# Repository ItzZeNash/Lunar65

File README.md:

# Lunar65
A keyboard made for personal use and sounds good, as I dont have a keyboard. 65% for optimal usability.
Render/Image

Images of Schem And PCB

# Build Guide

| No | Name | Spec | Quantity |
| ----- | ----- | ----- | ----- |
| 1 | Aluminum case | Aluminum | 1 |
| 2 | Main PCB | Hotswap socket compatible, 1.6 mm thick | 1 |
| 3 | Plate | Polycarbonate, 1.5mm thick | 1 |
| 4 | PCB foam | Poron, 3mm thick | 1 |
| 5 | Switch foam | Polyethylene or Poron, 0.5mm thick | 1 |
| 6 | Case foam | Poron, 1.5mm thick | 1 |
| 7 | Socket foam | Poron, 1.5mm thick | 1 |
| 8 | O-ring | AS568-264-VMQ-A30 | 1 |
| 9 | USB-C daughter board | [Unified Daughterboard C3](https://github.com/ai03-2725/Unified-Daughterboard) | 1 |
| 10 | JST cable | JST-SH, 4pin, double-side female connector, reverse direction, 10cm | 1 |
| 11 | Screws | m2 4mm, for USB-C daughter board | 4 |
| 12 | Rubber feet(Bumpons) | 3M SJ5302, diameter 8mm, height 2mm | 4 |

### Parts
| Name | Spec | Quantity |
| ----- | ----- | ----- |
| Key switch | CherryMX compatible key switch, 5pins(recommended) | 67 |
| Keycap | CherryMX compatible keycap, 1.75U Shift key(required) | 67 |
| Stabilizer | Durock V2, etc | 6.25U * 1set and 2U * 3set |
| USB cable | The connector on the keyboard side must be USB-C | 1 |
| Grease for lubrication | Krytox 205g0(recommended) | a few grams |

## Assembly Instructions
1. **Attaching rubber feet**  
   
   First attach the rubber feet to the aluminum case so that the bottom of the aluminum case is not scratched.  
   Attach the rubber feet according to the engraved circle on the four corners of the back of the aluminum case.  

1. **Pasting socket foam**  
   
   Pasting socket foam is difficult and cannot be redone.  
   There are two methods: one is to paste the entire surface and the other is to paste only a portion of the surface.  
   
   **Practice**  
   First, practice several times without peeling off the release paper on the adhesive surface.  
   
   Place the socket foam on a flat surface with the adhesive surface facing up.  
   Straighten any bent or floating parts.  
   
   Hold the four corners with the back side (part mounting surface) of the main PCB facing down.  
   Look at the main PCB from directly above, align the notch of the mount post with the main PCB, slowly put it on the foam.  

   **When pasting the entire surface**  
   Peel off the release paper on the socket foam, and paste the main PCB and socket foam according to the procedure you practiced.  
   Once pasted, it cannot be removed cleanly, so recommend not removing it, even if it is slightly displaced.  
   (even if it can be removed, the socket foam will be stretched and the position will not match)  
   
   **When pasting only a part**  
   Peel off only a part of the release paper and paste it.  
   The area to peel off is about 10 square mm per place, and the place to peel off is about 7-8 places where the width is not narrow.  
   Cut a part of the release paper with scissors and paste the main PCB and socket foam according to the procedure you practiced.

1. **Assembling the stabilizers**  
   Please refer to [this YouTube video](https://www.youtube.com/watch?v=-vhpHjlkRgQ).  
   Apply a little thick grease to the outside of the stem and the inside of the housing.  
   Insert the stem into the housing.  
   Apply a little thick grease from the tip of the wire to the part that bends at a right angle.  
   Insert the wire into the stem and fit the wire into the housing.  

1. **Installing stabilizers**  
   
   First, insert the side without screw holes into the larger stabilizer mounting holes on the main PCB.  
   Next, screw the side with screw holes from the back side of the main PCB.  
   Make sure that the stabilizer housing is not lifted off the main PCB and that there is no rattling.  

1. **Placing switch foam**  
   
   Place the switch foam on the main PCB.  
   Slide the switch foam so that it is under the stabilizer wires.  

1. **Placing PCB foam**  
   
   Place PCB foam on the main PCB in line with the stabilizer position.  

1. **Placing plate**
   
   Place the plate on the PCB foam, aligning it with the hole in the key switches.  

1. **Lubricating key switches**  
   Although not required, it is highly recommended to lubricate the key switches to improve the typing feels and sounds.  
   Please refer to [this YouTube video](https://www.youtube.com/watch?v=44Wv4OGdmu4).  

1. **Installing key switches**  
   
   Check that the holes in the switch foam align with the key switch pin holes on the main PCB.  
   Check that the pins of the key switch are straight and insert the key switch into the main PCB from the top of the plate.  
   (Be careful not to insert at an angle, as this may break the pins or damage the sockets)  
   Make sure that there are no gaps between the plate and the key switches, and between the key switches and the main PCB, viewed from the side, and that they are evenly installed.  

1. **Installing O-ring**  
   Install O-ring between main PCB and plate.  

   Around the backspace and spacebar keys, pass the O-ring through the top surface of the stabilizer, aligning it with the notch in the plate.  
   If the O-ring cannot be secured to the top of the stabilizer, proceed as is once it is in place, as it can be adjusted when the main PCB is installed in the case.  
   Make sure there is no gap and bend between the main PCB, O-ring and plate when viewed from the side.  

1. **Connecting JST cable to USB-C daughter board**  
   
   Connect JST cable to USB-C daughter board.  
   
   Since JST cable connectors have front and back sides, refer to the photo and insert the connector with the side with no exposed terminals facing up.    

1. **Installing USB-C daughter board**  
   
   With the surface of the USB-C daughter board (the side where the components are mounted) facing up, screw it into the center back of the aluminum case with four m2 4mm screws.  
   Grab the screws with tweezers to make it easier to screw them in.  

1. **Installing case foam**  
   
   Align the posts inside the aluminum case with the notches in the case foam, and put the case foam inside the aluminum case.    
   Pull the JST cable through the cutout in the case foam.  

1. **Connecting JST cable tom main PCB**  
   
   Insert the JST cable connector into the JST connector (beige color) on the back of the main PCB.  
   
   Since JST cable connectors have front and back sides, refer to the photo and insert the connector with the side with no exposed terminals facing up.    

1. **Installing main PCB to aluminum case**  
   
   With the back side of the main PCB slightly raised, pass the blocker of the aluminum case between the blocker of the main PCB and the O-ring.    
   Lift the entire main PCB slightly and put the O-ring on the front side of the main PCB over the post on the front side of the aluminum case (not visible).  
   Gently push the main PCB down until the O-ring lightly touches the post on the aluminum case (not visible).  
   
   Make sure the O-ring is not rolled up and coming out of  the plate.  

1. **Installing keycaps**  
   
   Installing the keycaps to the key switches.  

1. **Connecting USB cable**  
   
   Connect your USB cable to the keyboard and PC and now it is completed.

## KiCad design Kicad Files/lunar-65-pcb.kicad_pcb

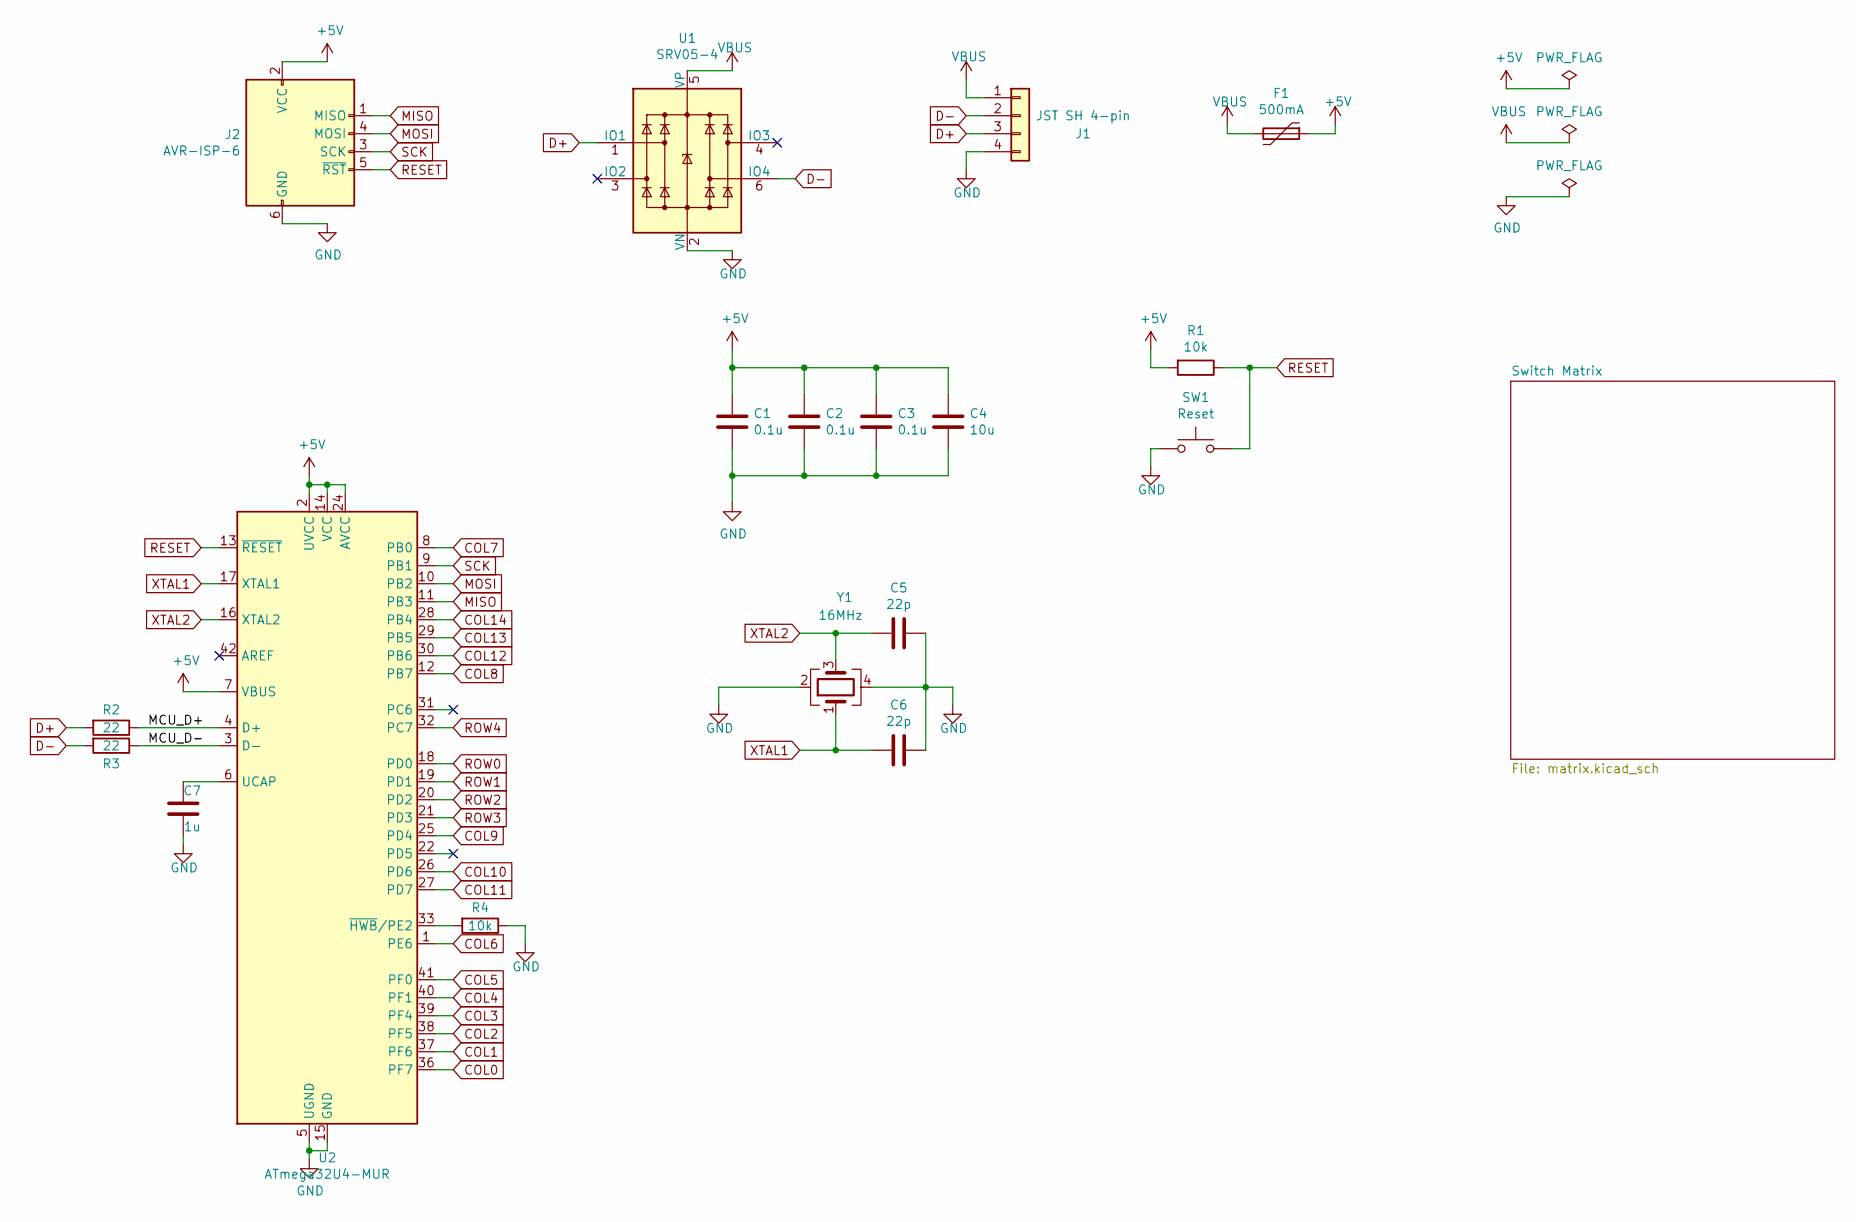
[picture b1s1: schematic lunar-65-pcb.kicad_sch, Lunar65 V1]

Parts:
C1, C2, C3: 0.1u; C_0805_2012Metric; LCSC Part # C49678
C4: 10u; C_0805_2012Metric; LCSC Part # C15850
C5, C6: 22p; C_0805_2012Metric; LCSC Part # C1804
C7: 1u; C_0805_2012Metric; LCSC Part # C28323
F1: 500mA; Fuse_1206_3216Metric; LCSC Part # C70076
J1: JST SH 4-pin; JST_SH_SM04B-SRSS-TB_1x04-1MP_P1.00mm_Horizontal; LCSC Part # C145956
J2: AVR-ISP-6; ISP
R1, R4: 10k; R_0805_2012Metric; LCSC Part # C17414
R2, R3: 22; R_0805_2012Metric; LCSC Part # C17561
SW1: Reset; SW_SPST_TL3342; LCSC Part # C318884
U1: SRV05-4; SOT-23-6; LCSC Part # C85364
U2: ATmega32U4-MUR; QFN-44-1EP_7x7mm_P0.5mm_EP5.2x5.2mm; LCSC Part # C45874
Y1: 16MHz; Crystal_SMD_3225-4Pin_3.2x2.5mm; LCSC Part # C13738

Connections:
+5V: C1.1, C2.1, C3.1, C4.1, F1.1, J2.2 (VCC), R1.2, U2.2 (UVCC), U2.7 (VBUS), U2.14 (VCC), U2.24 (AVCC), U2.34 (VCC), U2.44 (AVCC)
/MCU_D+: R2.1, U2.4 (D+)
/MCU_D-: R3.1, U2.3 (D-)
COL0: U2.36 (PF7); also elsewhere on the board
COL1: U2.37 (PF6); also elsewhere on the board
COL2: U2.38 (PF5); also elsewhere on the board
COL3: U2.39 (PF4); also elsewhere on the board
COL4: U2.40 (PF1); also elsewhere on the board
COL5: U2.41 (PF0); also elsewhere on the board
COL6: U2.1 (PE6); also elsewhere on the board
COL7: U2.8 (PB0); also elsewhere on the board
COL8: U2.12 (PB7); also elsewhere on the board
COL9: U2.25 (PD4); also elsewhere on the board
COL10: U2.26 (PD6); also elsewhere on the board
COL11: U2.27 (PD7); also elsewhere on the board
COL12: U2.30 (PB6); also elsewhere on the board
COL13: U2.29 (PB5); also elsewhere on the board
COL14: U2.28 (PB4); also elsewhere on the board
D+: J1.3, R2.2, U1.1 (IO1)
D-: J1.2, R3.2, U1.6 (IO4)
GND: C1.2, C2.2, C3.2, C4.2, C5.1, C6.1, C7.2, J1.4, J2.6 (GND), R4.1, SW1.1, U1.2 (VN), U2.5 (UGND), U2.15 (GND), U2.23 (GND), U2.35 (GND), U2.43 (GND), U2.45 (GND), Y1.2, Y1.4
MISO: J2.1 (MISO), U2.11 (PB3)
MOSI: J2.4 (MOSI), U2.10 (PB2)
unnamed: C7.1, U2.6 (UCAP)
unnamed: R4.2, U2.33 (~HWB/PE2)
RESET: J2.5 (~RST), R1.1, SW1.2, U2.13 (~RESET)
ROW0: U2.18 (PD0); also elsewhere on the board
ROW1: U2.19 (PD1); also elsewhere on the board
ROW2: U2.20 (PD2); also elsewhere on the board
ROW3: U2.21 (PD3); also elsewhere on the board
ROW4: U2.32 (PC7); also elsewhere on the board
SCK: J2.3 (SCK), U2.9 (PB1)
VBUS: F1.2, J1.1, U1.5 (VP)
XTAL1: C6.2, U2.17 (XTAL1), Y1.1
XTAL2: C5.2, U2.16 (XTAL2), Y1.3

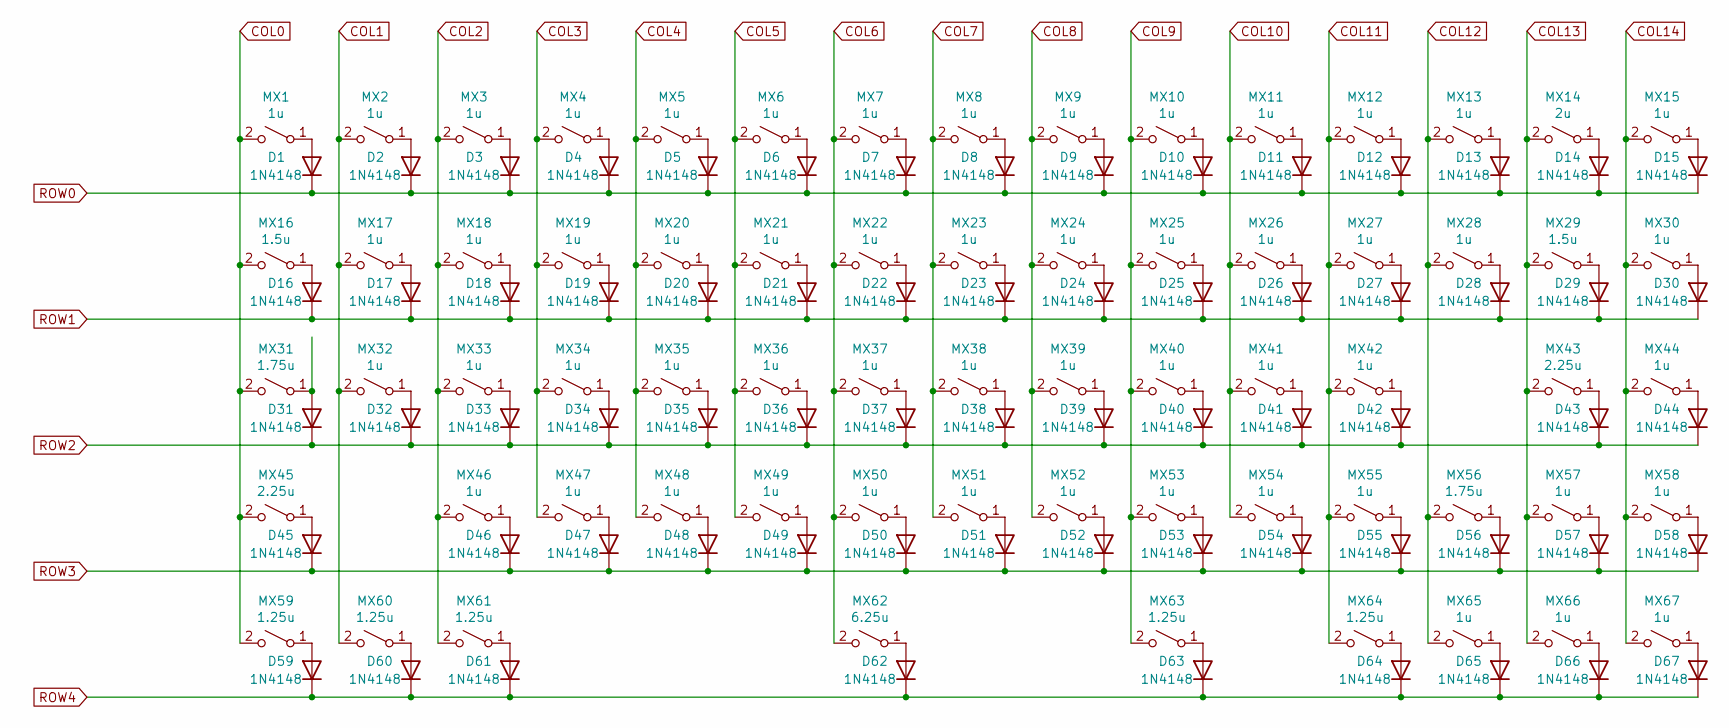
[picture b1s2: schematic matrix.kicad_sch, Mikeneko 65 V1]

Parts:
D1, D2, D3, D4, D5, D6, D7, D8, D9, D10, D11, D12, D13, D14, D15, D16, D17, D18, D19, D20, D21, D22, D23, D24, D25, D26, D27, D28, D29, D30, D31, D32, D33, D34, D35, D36, D37, D38, D39, D40, D41, D42, D43, D44, D45, D46, D47, D48, D49, D50, D51, D52, D53, D54, D55, D56, D57, D58, D59, D60, D61, D62, D63, D64, D65, D66, D67: 1N4148; D_SOD-123; LCSC Part # C81598
MX1, MX2, MX3, MX4, MX5, MX6, MX7, MX8, MX9, MX10, MX11, MX12, MX13, MX15, MX17, MX18, MX19, MX20, MX21, MX22, MX23, MX24, MX25, MX26, MX27, MX28, MX30, MX32, MX33, MX34, MX35, MX36, MX37, MX38, MX39, MX40, MX41, MX42, MX44, MX46, MX47, MX48, MX49, MX50, MX51, MX52, MX53, MX54, MX55, MX57, MX58, MX65, MX66, MX67: 1u; MXOnly-1U-Hotswap; LCSC Part # C2803348
MX14: 2u; MXOnly-2U-Hotswap; LCSC Part # C2803348
MX16, MX29: 1.5u; MXOnly-1.5U-Hotswap; LCSC Part # C2803348
MX31, MX56: 1.75u; MXOnly-1.75U-Hotswap; LCSC Part # C2803348
MX43, MX45: 2.25u; MXOnly-2.25U-Hotswap; LCSC Part # C2803348
MX59, MX60, MX61, MX63, MX64: 1.25u; MXOnly-1.25U-Hotswap; LCSC Part # C2803348
MX62: 6.25u; MXOnly-6.25U-Hotswap-ReversedStabilizers; LCSC Part # C2803348

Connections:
COL0: MX1.2 (B), MX16.2 (B), MX31.2 (B), MX45.2 (B), MX59.2 (B); also elsewhere on the board
COL1: MX2.2 (B), MX17.2 (B), MX32.2 (B), MX60.2 (B); also elsewhere on the board
COL2: MX3.2 (B), MX18.2 (B), MX33.2 (B), MX46.2 (B), MX61.2 (B); also elsewhere on the board
COL3: MX4.2 (B), MX19.2 (B), MX34.2 (B), MX47.2 (B); also elsewhere on the board
COL4: MX5.2 (B), MX20.2 (B), MX35.2 (B), MX48.2 (B); also elsewhere on the board
COL5: MX6.2 (B), MX21.2 (B), MX36.2 (B), MX49.2 (B); also elsewhere on the board
COL6: MX7.2 (B), MX22.2 (B), MX37.2 (B), MX50.2 (B), MX62.2 (B); also elsewhere on the board
COL7: MX8.2 (B), MX23.2 (B), MX38.2 (B), MX51.2 (B); also elsewhere on the board
COL8: MX9.2 (B), MX24.2 (B), MX39.2 (B), MX52.2 (B); also elsewhere on the board
COL9: MX10.2 (B), MX25.2 (B), MX40.2 (B), MX53.2 (B), MX63.2 (B); also elsewhere on the board
COL10: MX11.2 (B), MX26.2 (B), MX41.2 (B), MX54.2 (B); also elsewhere on the board
COL11: MX12.2 (B), MX27.2 (B), MX42.2 (B), MX55.2 (B), MX64.2 (B); also elsewhere on the board
COL12: MX13.2 (B), MX28.2 (B), MX56.2 (B), MX65.2 (B); also elsewhere on the board
COL13: MX14.2 (B), MX29.2 (B), MX43.2 (B), MX57.2 (B), MX66.2 (B); also elsewhere on the board
COL14: MX15.2 (B), MX30.2 (B), MX44.2 (B), MX58.2 (B), MX67.2 (B); also elsewhere on the board
unnamed: D1.2 (A), MX1.1 (A)
unnamed: D2.2 (A), MX2.1 (A)
unnamed: D3.2 (A), MX3.1 (A)
unnamed: D4.2 (A), MX4.1 (A)
unnamed: D5.2 (A), MX5.1 (A)
unnamed: D6.2 (A), MX6.1 (A)
unnamed: D7.2 (A), MX7.1 (A)
unnamed: D8.2 (A), MX8.1 (A)
unnamed: D9.2 (A), MX9.1 (A)
unnamed: D10.2 (A), MX10.1 (A)
unnamed: D11.2 (A), MX11.1 (A)
unnamed: D12.2 (A), MX12.1 (A)
unnamed: D13.2 (A), MX13.1 (A)
unnamed: D14.2 (A), MX14.1 (A)
unnamed: D15.2 (A), MX15.1 (A)
unnamed: D16.2 (A), MX16.1 (A)
unnamed: D17.2 (A), MX17.1 (A)
unnamed: D18.2 (A), MX18.1 (A)
unnamed: D19.2 (A), MX19.1 (A)
unnamed: D20.2 (A), MX20.1 (A)
unnamed: D21.2 (A), MX21.1 (A)
unnamed: D22.2 (A), MX22.1 (A)
unnamed: D23.2 (A), MX23.1 (A)
unnamed: D24.2 (A), MX24.1 (A)
unnamed: D25.2 (A), MX25.1 (A)
unnamed: D26.2 (A), MX26.1 (A)
unnamed: D27.2 (A), MX27.1 (A)
unnamed: D28.2 (A), MX28.1 (A)
unnamed: D29.2 (A), MX29.1 (A)
unnamed: D30.2 (A), MX30.1 (A)
unnamed: D31.2 (A), MX31.1 (A)
unnamed: D32.2 (A), MX32.1 (A)
unnamed: D33.2 (A), MX33.1 (A)
unnamed: D34.2 (A), MX34.1 (A)
unnamed: D35.2 (A), MX35.1 (A)
unnamed: D36.2 (A), MX36.1 (A)
unnamed: D37.2 (A), MX37.1 (A)
unnamed: D38.2 (A), MX38.1 (A)
unnamed: D39.2 (A), MX39.1 (A)
unnamed: D40.2 (A), MX40.1 (A)
unnamed: D41.2 (A), MX41.1 (A)
unnamed: D42.2 (A), MX42.1 (A)
unnamed: D43.2 (A), MX43.1 (A)
unnamed: D44.2 (A), MX44.1 (A)
unnamed: D45.2 (A), MX45.1 (A)
unnamed: D46.2 (A), MX46.1 (A)
unnamed: D47.2 (A), MX47.1 (A)
unnamed: D48.2 (A), MX48.1 (A)
unnamed: D49.2 (A), MX49.1 (A)
unnamed: D50.2 (A), MX50.1 (A)
unnamed: D51.2 (A), MX51.1 (A)
unnamed: D52.2 (A), MX52.1 (A)
unnamed: D53.2 (A), MX53.1 (A)
unnamed: D54.2 (A), MX54.1 (A)
unnamed: D55.2 (A), MX55.1 (A)
unnamed: D56.2 (A), MX56.1 (A)
unnamed: D57.2 (A), MX57.1 (A)
unnamed: D58.2 (A), MX58.1 (A)
unnamed: D59.2 (A), MX59.1 (A)
unnamed: D60.2 (A), MX60.1 (A)
unnamed: D61.2 (A), MX61.1 (A)
unnamed: D62.2 (A), MX62.1 (A)
unnamed: D63.2 (A), MX63.1 (A)
unnamed: D64.2 (A), MX64.1 (A)
unnamed: D65.2 (A), MX65.1 (A)
unnamed: D66.2 (A), MX66.1 (A)
unnamed: D67.2 (A), MX67.1 (A)
ROW0: D1.1 (K), D2.1 (K), D3.1 (K), D4.1 (K), D5.1 (K), D6.1 (K), D7.1 (K), D8.1 (K), D9.1 (K), D10.1 (K), D11.1 (K), D12.1 (K), D13.1 (K), D14.1 (K), D15.1 (K); also elsewhere on the board
ROW1: D16.1 (K), D17.1 (K), D18.1 (K), D19.1 (K), D20.1 (K), D21.1 (K), D22.1 (K), D23.1 (K), D24.1 (K), D25.1 (K), D26.1 (K), D27.1 (K), D28.1 (K), D29.1 (K), D30.1 (K); also elsewhere on the board
ROW2: D31.1 (K), D32.1 (K), D33.1 (K), D34.1 (K), D35.1 (K), D36.1 (K), D37.1 (K), D38.1 (K), D39.1 (K), D40.1 (K), D41.1 (K), D42.1 (K), D43.1 (K), D44.1 (K); also elsewhere on the board
ROW3: D45.1 (K), D46.1 (K), D47.1 (K), D48.1 (K), D49.1 (K), D50.1 (K), D51.1 (K), D52.1 (K), D53.1 (K), D54.1 (K), D55.1 (K), D56.1 (K), D57.1 (K), D58.1 (K); also elsewhere on the board
ROW4: D59.1 (K), D60.1 (K), D61.1 (K), D62.1 (K), D63.1 (K), D64.1 (K), D65.1 (K), D66.1 (K), D67.1 (K); also elsewhere on the board

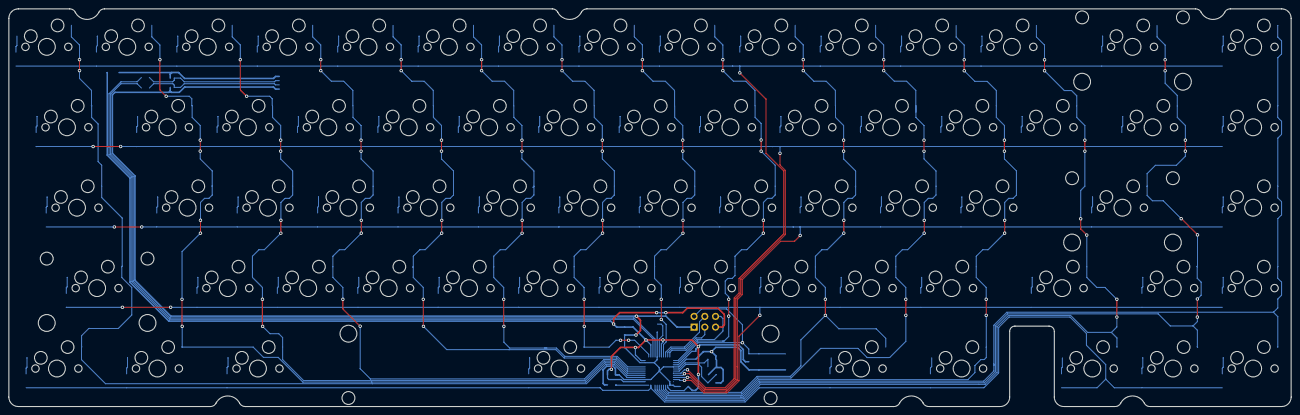
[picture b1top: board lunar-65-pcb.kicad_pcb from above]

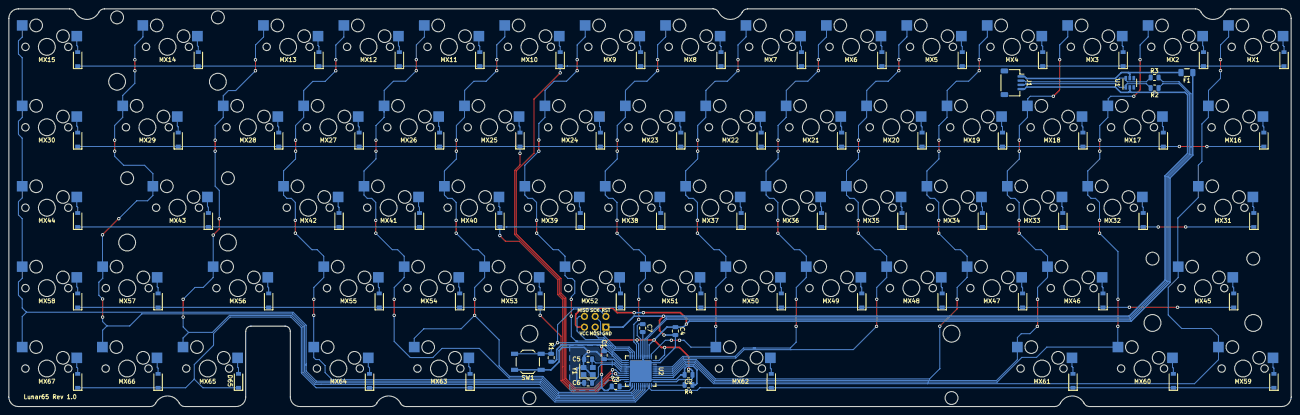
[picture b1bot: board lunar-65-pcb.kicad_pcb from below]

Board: 2 copper layers, 303.8 x 94.2 mm, 152 parts (84 on the bottom side), 102 nets.

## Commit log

2026-04-01 Create temp
2026-04-01 Update README with images of Lunar65 keyboard
    Added images of the keyboard and its schematics.
2026-04-01 Add build guide and assembly instructions to README
    Added a detailed build guide with parts list and assembly instructions.
2026-04-01 Enhance Build Guide with more images
    Added additional images to the Build Guide section.

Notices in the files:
Kicad Files/lunar-65-pcb.kicad_sch:
Copyright © 2020 kkatano
MIT License
